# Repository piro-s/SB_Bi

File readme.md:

# SB_Bi:  
A simple rectifier board for a transformer with two secondary windings with a  
common point. If you don’t need the 220V part, then break it off (for  
convenience, there is a fuse holder on the board and a lead to the toggle  
switch).  

### Schemes:  
###### sb_bi_v0.1:  
[pdf](docs/sb_bi_v0.1.pdf)  

### Images:  
###### sb_bi_v0.1:  
top:  
  
bottom:  
  
assembly:  

###### gerber:  
Archive for production:  
[sb_bi_v0.1](https://github.com/piro-s/SB_Bi/raw/main/gerber/sb_bi_v0.1.zip)

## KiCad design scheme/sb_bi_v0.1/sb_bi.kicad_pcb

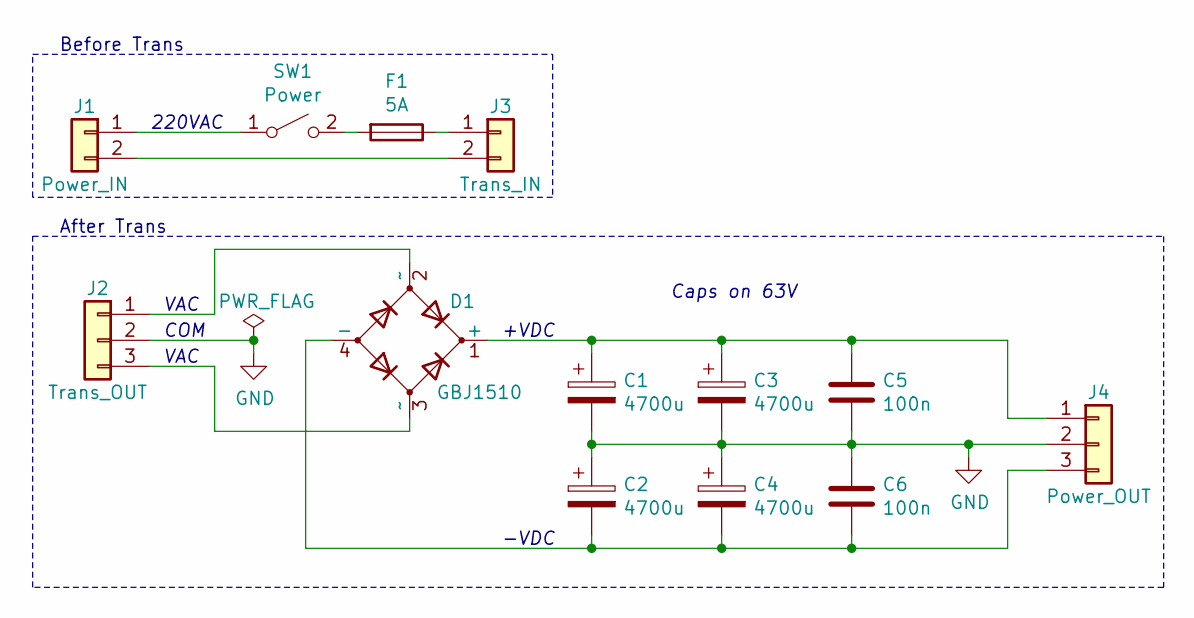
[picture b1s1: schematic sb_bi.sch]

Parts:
C1, C2, C3, C4: 4700u; CP_Radial_D18.0mm_P7.50mm
C5, C6: 100n; C_Axial_L5.1mm_D3.1mm_P7.50mm_Horizontal
D1: GBJ1510; GBJ
F1: 5A; Fuseholder_Cylinder-5x20mm_Schurter_0031_8201_Horizontal_Op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
J1: Power_IN; SolderWire-0.5sqmm_1x02_P4.6mm_D0.9mm_OD2.1mm
J2: Trans_OUT; SolderWire-0.5sqmm_1x03_P4.6mm_D0.9mm_OD2.1mm
J3: Trans_IN; SolderWire-0.5sqmm_1x02_P4.6mm_D0.9mm_OD2.1mm
J4: Power_OUT; SolderWire-0.5sqmm_1x03_P4.6mm_D0.9mm_OD2.1mm
SW1: Power; SolderWire-0.5sqmm_1x02_P4.6mm_D0.9mm_OD2.1mm

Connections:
GND: C1.2, C2.1, C3.2, C4.1, C5.2, C6.1, J2.2, J4.2
unnamed: C1.1, C3.1, C5.1, D1.1 (+), J4.1
unnamed: C2.2, C4.2, C6.2, D1.4 (-), J4.3
unnamed: D1.2 (~~), J2.1
unnamed: D1.3 (~~), J2.3
unnamed: F1.1, J3.1
unnamed: F1.2, SW1.2 (B)
unnamed: J1.1, SW1.1 (A)
unnamed: J1.2, J3.2

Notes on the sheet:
220VAC
+VDC
-VDC
COM
VAC
Before Trans
After Trans
Caps on 63V

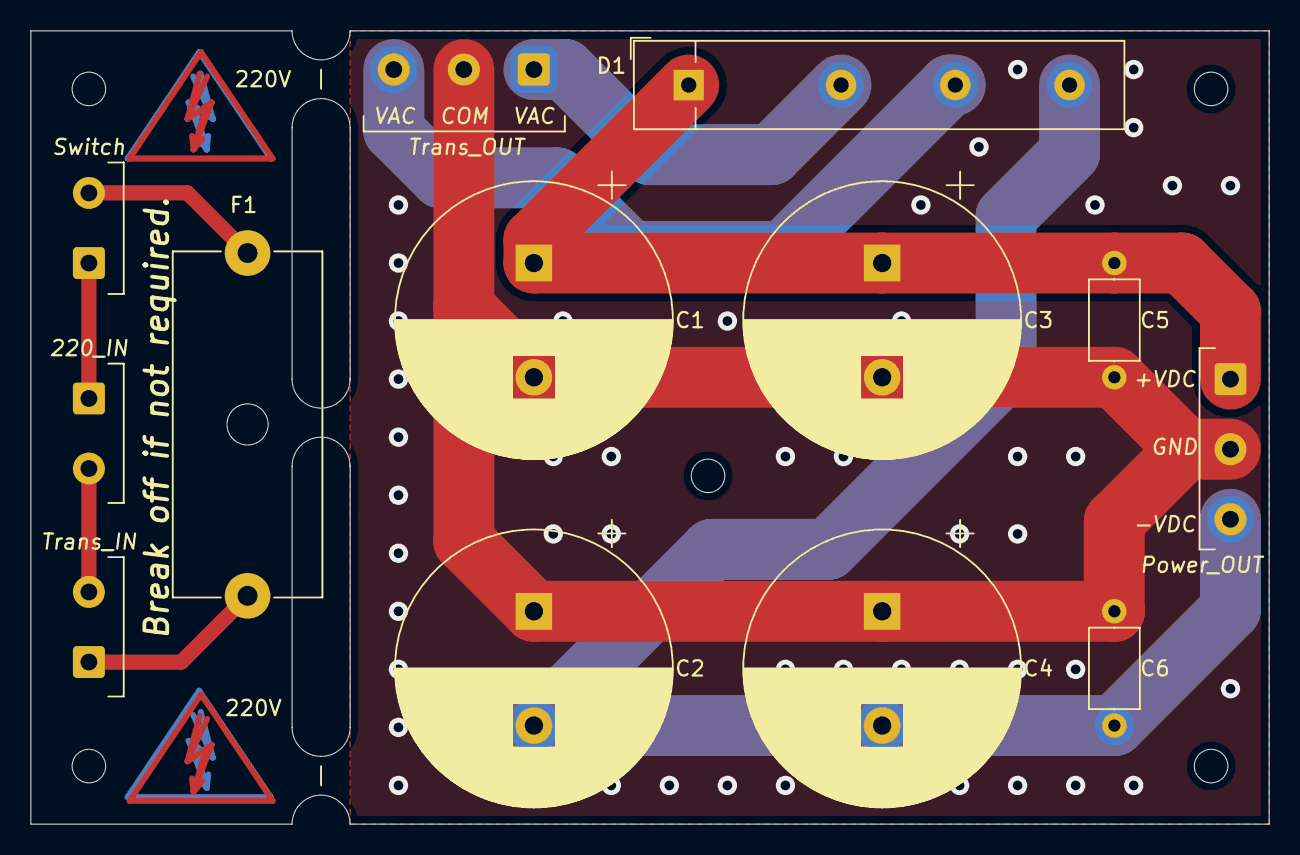
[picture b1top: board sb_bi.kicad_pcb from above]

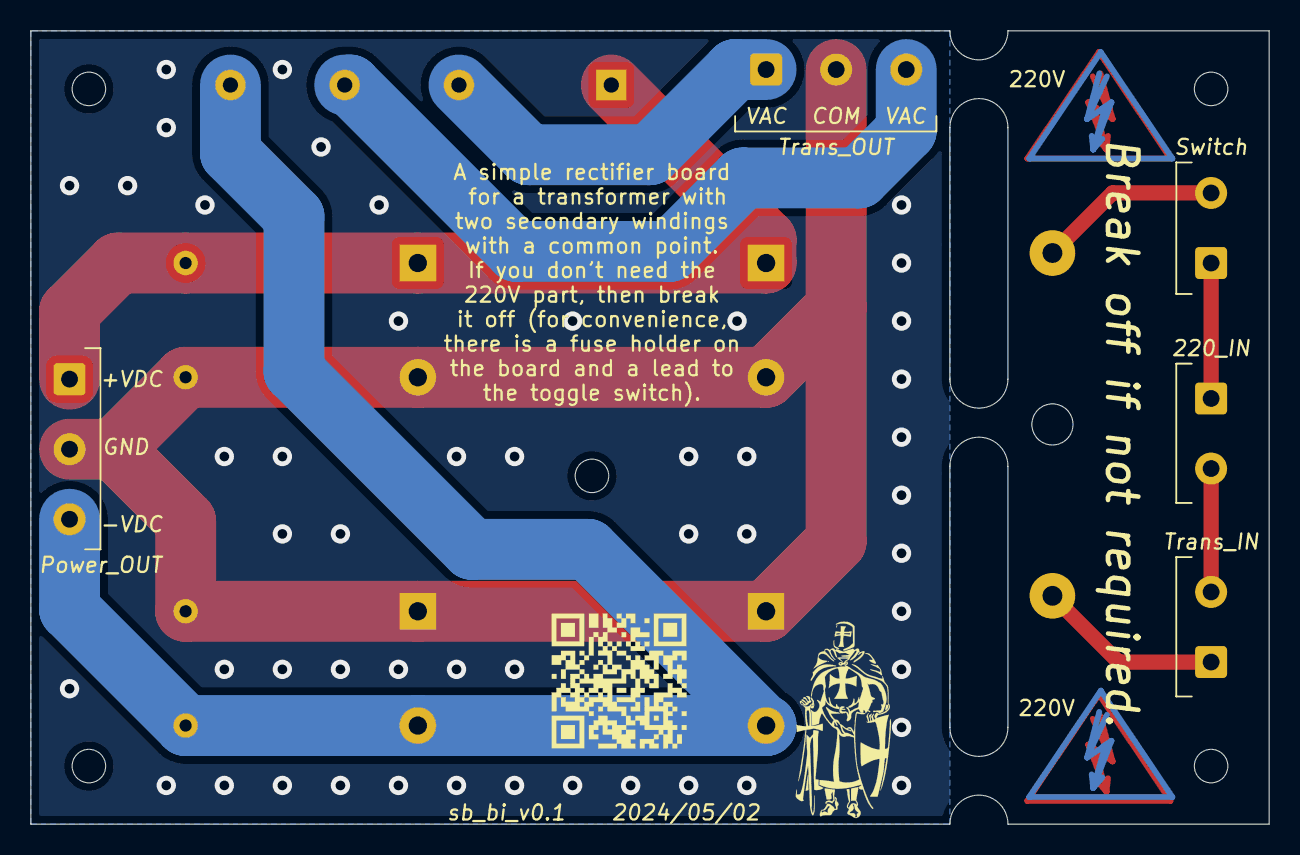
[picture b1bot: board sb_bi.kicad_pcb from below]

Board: 2 copper layers, 81.3 x 52.1 mm, 17 parts (2 on the bottom side), 9 nets.

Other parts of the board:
220V, 220V#2, 220V#3, 220V#4: Symbol_HighVoltage_Type2_CopperTop_VerySmall

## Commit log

2024-05-02 Initial
